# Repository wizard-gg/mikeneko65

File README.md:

# Mikeneko 65 V4

A simple 65% keyboard for DIYers. This project was derived from [kkatano's Bakeneko 65](https://github.com/kkatano/bakeneko-65).

## Updates

### Differences between Mikeneko 65 V3 and V4

- Switched pcb style from soldering to hotswap

### Differences between Bakeneko 65 V3 and Mikeneko 65 V3

- Added support for PCB screw ins stabilizer
- Switched MCU to ATmega32U4-MU(R) to cope with MCU supply shortage

## Features

- Single piece tray case
- O-ring gasket mount (Friction fit)
- [Unified Daughterboard](https://github.com/ai03-2725/Unified-Daughterboard) or [Simplified Daughterboard](https://github.com/kb-elmo/simplified-daughterboard)
- QMK firmware and VIA (For now, you can use Bakeneko 65's firmware as is)
- PCB designed with KiCAD 5.1.4

## Layouts

## Specs

- Dimensions: 315 x 110 x 30mm
- Front height: 18.5mm
- Home row height: 31mm(with GMK keycaps and bumpons)
- Typing angle: 6 degree
- Weight:
  - PLA Case: 390g
  - Aluminum Case: 760g
- O-ring gasket: VMQ-50(Silicone 50 duro) AS568-264

## Notes

- All files are to be used at your own risk
- As for stabilizers, both PCB snap ins and screw ins are supported

## Resources

- Documents: https://drive.google.com/drive/folders/1tddSihOS8Pgf1lTQOjHohYCl8efxXIeH
  - For now, you can refer Bakeneko 65's documents as is
  - Parts guide and other useful information
- Discord: https://discord.com/channels/927936241805189171/
  - Have fun with community members
  - Talk about Mikeneko builds and mods, and share your works
  - You can also contact me from there

## Special thanks to

- **kkatano** Open-sourced Bakeneko 65 and answered my questions in his community
- People who supported the development of Bakeneko series

## Also I should mention
- Many keyboard community members for giving me advice and feedback, thanks!

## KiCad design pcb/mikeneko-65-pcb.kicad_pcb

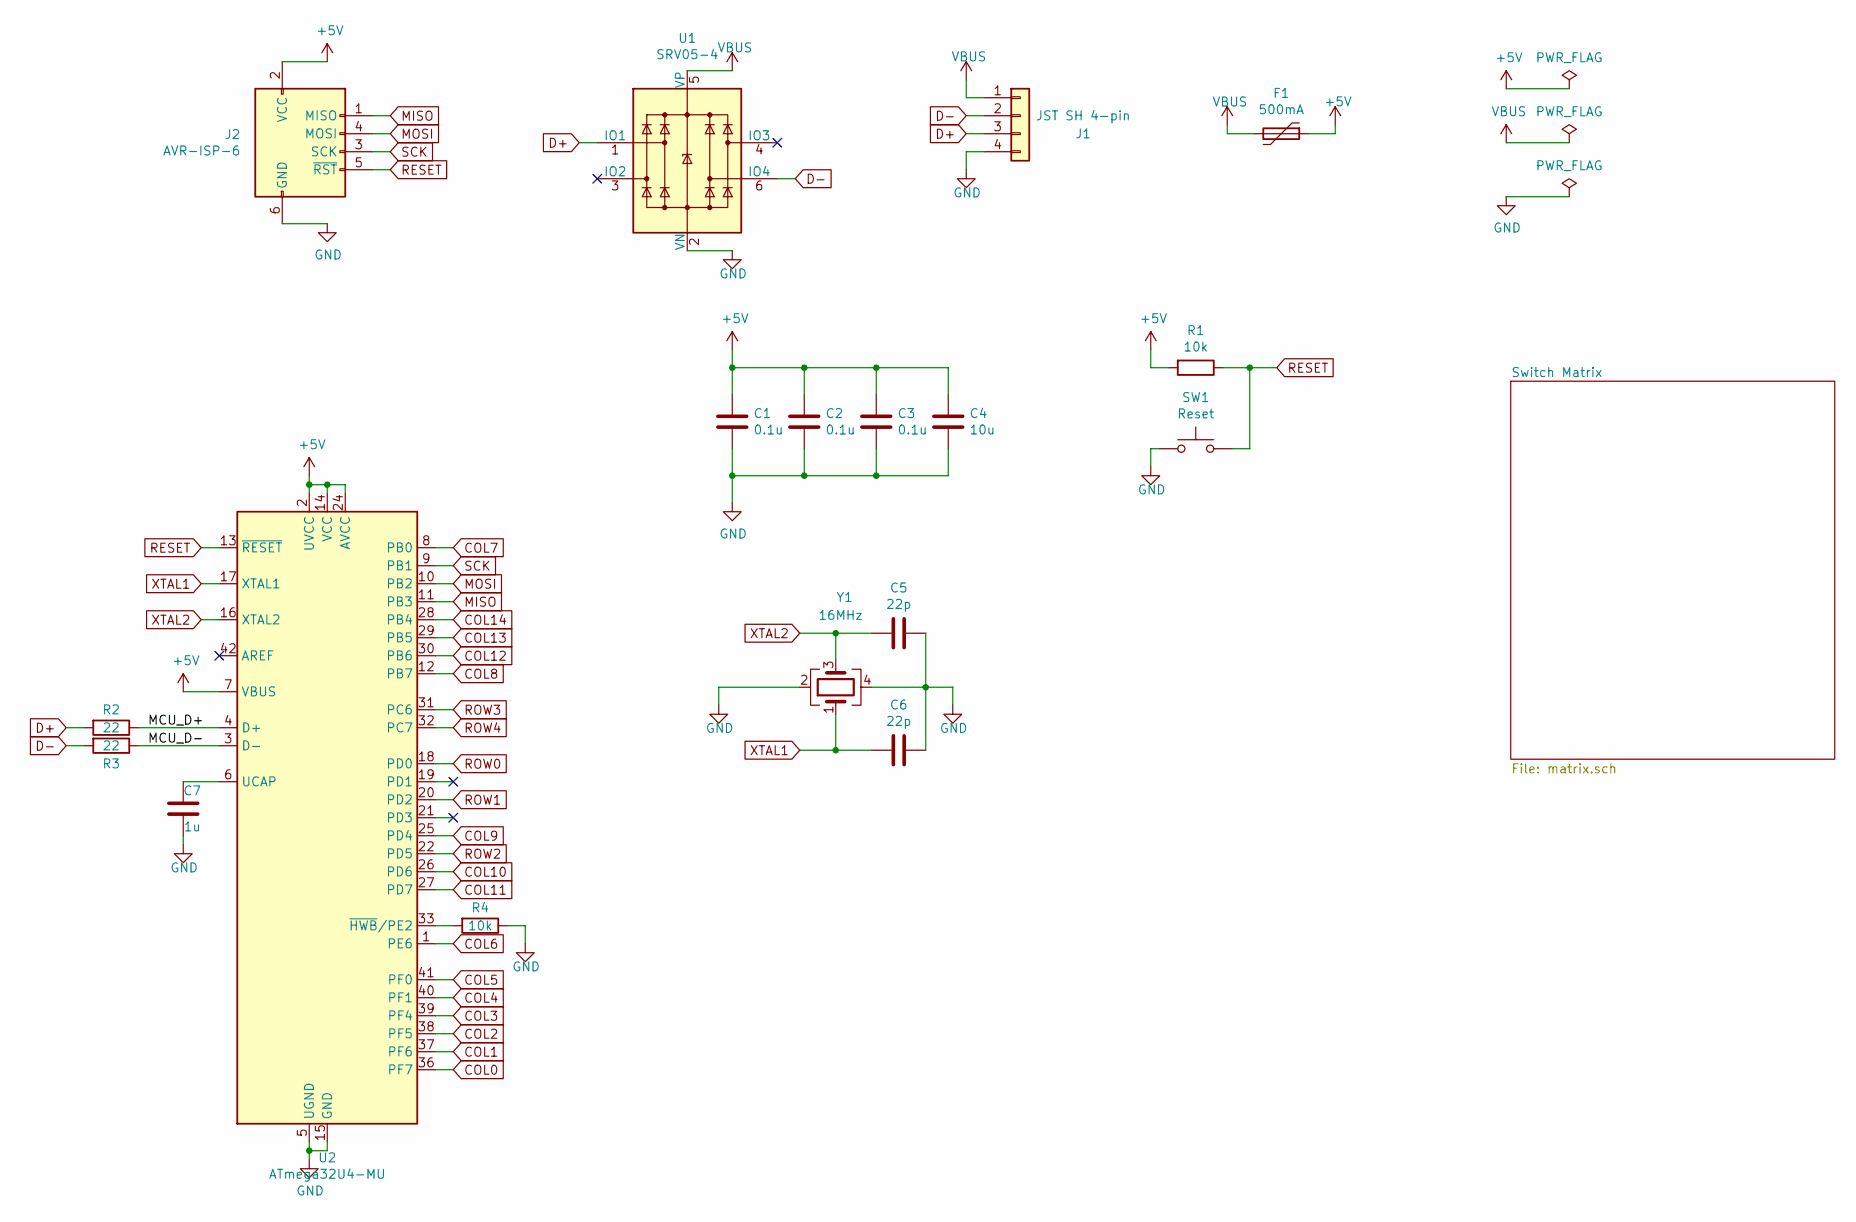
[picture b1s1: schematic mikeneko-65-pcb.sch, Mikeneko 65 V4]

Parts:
C1, C2, C3: 0.1u; C_0805_2012Metric; LCSC Part # C49678
C4: 10u; C_0805_2012Metric; LCSC Part # C15850
C5, C6: 22p; C_0805_2012Metric; LCSC Part # C1804
C7: 1u; C_0805_2012Metric; LCSC Part # C28323
F1: 500mA; Fuse_1206_3216Metric; LCSC Part # C70076
J1: JST SH 4-pin; JST_SH_SM04B-SRSS-TB_1x04-1MP_P1.00mm_Horizontal; LCSC Part # C160404
J2: AVR-ISP-6; ISP
R1, R4: 10k; R_0805_2012Metric; LCSC Part # C17414
R2, R3: 22; R_0805_2012Metric; LCSC Part # C17561
SW1: Reset; SW_SPST_TL3342; LCSC Part # C318884
U1: SRV05-4; SOT-23-6; LCSC Part # C85364
U2: ATmega32U4-MU; QFN-44-1EP_7x7mm_P0.5mm_EP5.2x5.2mm
Y1: 16MHz; Crystal_SMD_3225-4Pin_3.2x2.5mm; LCSC Part # C13738

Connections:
+5V: C1.1, C2.1, C3.1, C4.1, F1.1, J2.2 (VCC), R1.2, U2.2 (UVCC), U2.7 (VBUS), U2.14 (VCC), U2.24 (AVCC), U2.34 (VCC), U2.44 (AVCC)
/MCU_D+: R2.1, U2.4 (D+)
/MCU_D-: R3.1, U2.3 (D-)
COL0: U2.36 (PF7); also elsewhere on the board
COL1: U2.37 (PF6); also elsewhere on the board
COL2: U2.38 (PF5); also elsewhere on the board
COL3: U2.39 (PF4); also elsewhere on the board
COL4: U2.40 (PF1); also elsewhere on the board
COL5: U2.41 (PF0); also elsewhere on the board
COL6: U2.1 (PE6); also elsewhere on the board
COL7: U2.8 (PB0); also elsewhere on the board
COL8: U2.12 (PB7); also elsewhere on the board
COL9: U2.25 (PD4); also elsewhere on the board
COL10: U2.26 (PD6); also elsewhere on the board
COL11: U2.27 (PD7); also elsewhere on the board
COL12: U2.30 (PB6); also elsewhere on the board
COL13: U2.29 (PB5); also elsewhere on the board
COL14: U2.28 (PB4); also elsewhere on the board
D+: J1.3, R2.2, U1.1 (IO1)
D-: J1.2, R3.2, U1.6 (IO4)
GND: C1.2, C2.2, C3.2, C4.2, C5.1, C6.1, C7.2, J1.4, J2.6 (GND), R4.1, SW1.1, U1.2 (VN), U2.5 (UGND), U2.15 (GND), U2.23 (GND), U2.35 (GND), U2.43 (GND), U2.45 (GND), Y1.2, Y1.4
MISO: J2.1 (MISO), U2.11 (PB3)
MOSI: J2.4 (MOSI), U2.10 (PB2)
unnamed: C7.1, U2.6 (UCAP)
unnamed: R4.2, U2.33 (~HWB~/PE2)
RESET: J2.5 (~RST), R1.1, SW1.2, U2.13 (~RESET)
ROW0: U2.18 (PD0); also elsewhere on the board
ROW1: U2.20 (PD2); also elsewhere on the board
ROW2: U2.22 (PD5); also elsewhere on the board
ROW3: U2.31 (PC6); also elsewhere on the board
ROW4: U2.32 (PC7); also elsewhere on the board
SCK: J2.3 (SCK), U2.9 (PB1)
VBUS: F1.2, J1.1, U1.5 (VP)
XTAL1: C6.2, U2.17 (XTAL1), Y1.1
XTAL2: C5.2, U2.16 (XTAL2), Y1.3

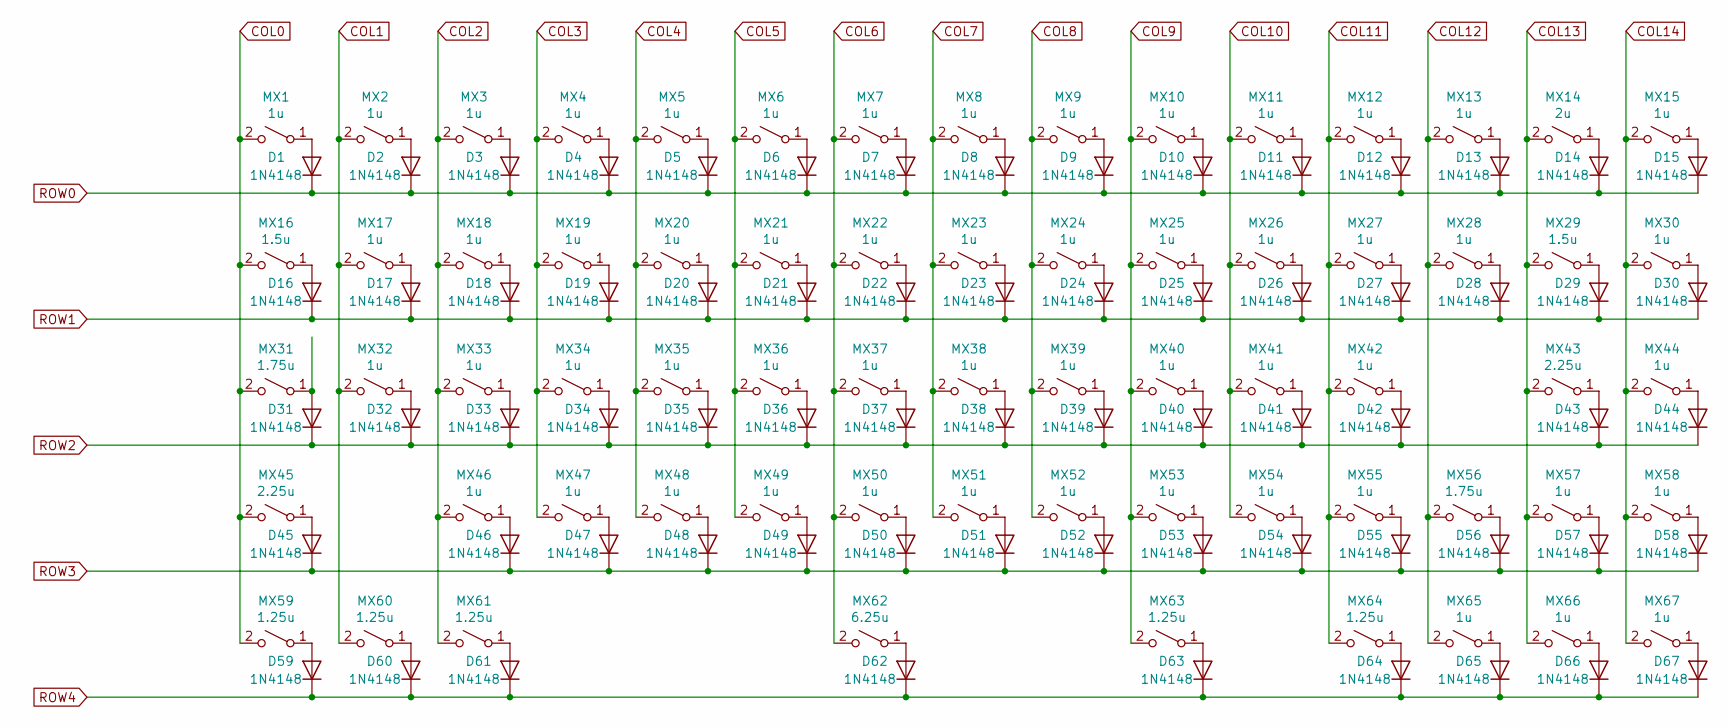
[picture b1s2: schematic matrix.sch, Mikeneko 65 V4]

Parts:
D1, D2, D3, D4, D5, D6, D7, D8, D9, D10, D11, D12, D13, D14, D15, D16, D17, D18, D19, D20, D21, D22, D23, D24, D25, D26, D27, D28, D29, D30, D31, D32, D33, D34, D35, D36, D37, D38, D39, D40, D41, D42, D43, D44, D45, D46, D47, D48, D49, D50, D51, D52, D53, D54, D55, D56, D57, D58, D59, D60, D61, D62, D63, D64, D65, D66, D67: 1N4148; D_SOD-123; LCSC Part # C81598
MX1, MX2, MX3, MX4, MX5, MX6, MX7, MX8, MX9, MX10, MX11, MX12, MX13, MX15, MX17, MX18, MX19, MX20, MX21, MX22, MX23, MX24, MX25, MX26, MX27, MX28, MX30, MX32, MX33, MX34, MX35, MX36, MX37, MX38, MX39, MX40, MX41, MX42, MX44, MX46, MX47, MX48, MX49, MX50, MX51, MX52, MX53, MX54, MX55, MX57, MX58, MX65, MX66, MX67: 1u; MXOnly-1U-Hotswap
MX14: 2u; MXOnly-2U-Hotswap
MX16, MX29: 1.5u; MXOnly-1.5U-Hotswap
MX31, MX56: 1.75u; MXOnly-1.75U-Hotswap
MX43, MX45: 2.25u; MXOnly-2.25U-Hotswap
MX59, MX60, MX61, MX63, MX64: 1.25u; MXOnly-1.25U-Hotswap
MX62: 6.25u; MXOnly-6.25U-Hotswap-ReversedStabilizers

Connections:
COL0: MX1.2 (B), MX16.2 (B), MX31.2 (B), MX45.2 (B), MX59.2 (B); also elsewhere on the board
COL1: MX2.2 (B), MX17.2 (B), MX32.2 (B), MX60.2 (B); also elsewhere on the board
COL2: MX3.2 (B), MX18.2 (B), MX33.2 (B), MX46.2 (B), MX61.2 (B); also elsewhere on the board
COL3: MX4.2 (B), MX19.2 (B), MX34.2 (B), MX47.2 (B); also elsewhere on the board
COL4: MX5.2 (B), MX20.2 (B), MX35.2 (B), MX48.2 (B); also elsewhere on the board
COL5: MX6.2 (B), MX21.2 (B), MX36.2 (B), MX49.2 (B); also elsewhere on the board
COL6: MX7.2 (B), MX22.2 (B), MX37.2 (B), MX50.2 (B), MX62.2 (B); also elsewhere on the board
COL7: MX8.2 (B), MX23.2 (B), MX38.2 (B), MX51.2 (B); also elsewhere on the board
COL8: MX9.2 (B), MX24.2 (B), MX39.2 (B), MX52.2 (B); also elsewhere on the board
COL9: MX10.2 (B), MX25.2 (B), MX40.2 (B), MX53.2 (B), MX63.2 (B); also elsewhere on the board
COL10: MX11.2 (B), MX26.2 (B), MX41.2 (B), MX54.2 (B); also elsewhere on the board
COL11: MX12.2 (B), MX27.2 (B), MX42.2 (B), MX55.2 (B), MX64.2 (B); also elsewhere on the board
COL12: MX13.2 (B), MX28.2 (B), MX56.2 (B), MX65.2 (B); also elsewhere on the board
COL13: MX14.2 (B), MX29.2 (B), MX43.2 (B), MX57.2 (B), MX66.2 (B); also elsewhere on the board
COL14: MX15.2 (B), MX30.2 (B), MX44.2 (B), MX58.2 (B), MX67.2 (B); also elsewhere on the board
unnamed: D1.2 (A), MX1.1 (A)
unnamed: D2.2 (A), MX2.1 (A)
unnamed: D3.2 (A), MX3.1 (A)
unnamed: D4.2 (A), MX4.1 (A)
unnamed: D5.2 (A), MX5.1 (A)
unnamed: D6.2 (A), MX6.1 (A)
unnamed: D7.2 (A), MX7.1 (A)
unnamed: D8.2 (A), MX8.1 (A)
unnamed: D9.2 (A), MX9.1 (A)
unnamed: D10.2 (A), MX10.1 (A)
unnamed: D11.2 (A), MX11.1 (A)
unnamed: D12.2 (A), MX12.1 (A)
unnamed: D13.2 (A), MX13.1 (A)
unnamed: D14.2 (A), MX14.1 (A)
unnamed: D15.2 (A), MX15.1 (A)
unnamed: D16.2 (A), MX16.1 (A)
unnamed: D17.2 (A), MX17.1 (A)
unnamed: D18.2 (A), MX18.1 (A)
unnamed: D19.2 (A), MX19.1 (A)
unnamed: D20.2 (A), MX20.1 (A)
unnamed: D21.2 (A), MX21.1 (A)
unnamed: D22.2 (A), MX22.1 (A)
unnamed: D23.2 (A), MX23.1 (A)
unnamed: D24.2 (A), MX24.1 (A)
unnamed: D25.2 (A), MX25.1 (A)
unnamed: D26.2 (A), MX26.1 (A)
unnamed: D27.2 (A), MX27.1 (A)
unnamed: D28.2 (A), MX28.1 (A)
unnamed: D29.2 (A), MX29.1 (A)
unnamed: D30.2 (A), MX30.1 (A)
unnamed: D31.2 (A), MX31.1 (A)
unnamed: D32.2 (A), MX32.1 (A)
unnamed: D33.2 (A), MX33.1 (A)
unnamed: D34.2 (A), MX34.1 (A)
unnamed: D35.2 (A), MX35.1 (A)
unnamed: D36.2 (A), MX36.1 (A)
unnamed: D37.2 (A), MX37.1 (A)
unnamed: D38.2 (A), MX38.1 (A)
unnamed: D39.2 (A), MX39.1 (A)
unnamed: D40.2 (A), MX40.1 (A)
unnamed: D41.2 (A), MX41.1 (A)
unnamed: D42.2 (A), MX42.1 (A)
unnamed: D43.2 (A), MX43.1 (A)
unnamed: D44.2 (A), MX44.1 (A)
unnamed: D45.2 (A), MX45.1 (A)
unnamed: D46.2 (A), MX46.1 (A)
unnamed: D47.2 (A), MX47.1 (A)
unnamed: D48.2 (A), MX48.1 (A)
unnamed: D49.2 (A), MX49.1 (A)
unnamed: D50.2 (A), MX50.1 (A)
unnamed: D51.2 (A), MX51.1 (A)
unnamed: D52.2 (A), MX52.1 (A)
unnamed: D53.2 (A), MX53.1 (A)
unnamed: D54.2 (A), MX54.1 (A)
unnamed: D55.2 (A), MX55.1 (A)
unnamed: D56.2 (A), MX56.1 (A)
unnamed: D57.2 (A), MX57.1 (A)
unnamed: D58.2 (A), MX58.1 (A)
unnamed: D59.2 (A), MX59.1 (A)
unnamed: D60.2 (A), MX60.1 (A)
unnamed: D61.2 (A), MX61.1 (A)
unnamed: D62.2 (A), MX62.1 (A)
unnamed: D63.2 (A), MX63.1 (A)
unnamed: D64.2 (A), MX64.1 (A)
unnamed: D65.2 (A), MX65.1 (A)
unnamed: D66.2 (A), MX66.1 (A)
unnamed: D67.2 (A), MX67.1 (A)
ROW0: D1.1 (K), D2.1 (K), D3.1 (K), D4.1 (K), D5.1 (K), D6.1 (K), D7.1 (K), D8.1 (K), D9.1 (K), D10.1 (K), D11.1 (K), D12.1 (K), D13.1 (K), D14.1 (K), D15.1 (K); also elsewhere on the board
ROW1: D16.1 (K), D17.1 (K), D18.1 (K), D19.1 (K), D20.1 (K), D21.1 (K), D22.1 (K), D23.1 (K), D24.1 (K), D25.1 (K), D26.1 (K), D27.1 (K), D28.1 (K), D29.1 (K), D30.1 (K); also elsewhere on the board
ROW2: D31.1 (K), D32.1 (K), D33.1 (K), D34.1 (K), D35.1 (K), D36.1 (K), D37.1 (K), D38.1 (K), D39.1 (K), D40.1 (K), D41.1 (K), D42.1 (K), D43.1 (K), D44.1 (K); also elsewhere on the board
ROW3: D45.1 (K), D46.1 (K), D47.1 (K), D48.1 (K), D49.1 (K), D50.1 (K), D51.1 (K), D52.1 (K), D53.1 (K), D54.1 (K), D55.1 (K), D56.1 (K), D57.1 (K), D58.1 (K); also elsewhere on the board
ROW4: D59.1 (K), D60.1 (K), D61.1 (K), D62.1 (K), D63.1 (K), D64.1 (K), D65.1 (K), D66.1 (K), D67.1 (K); also elsewhere on the board

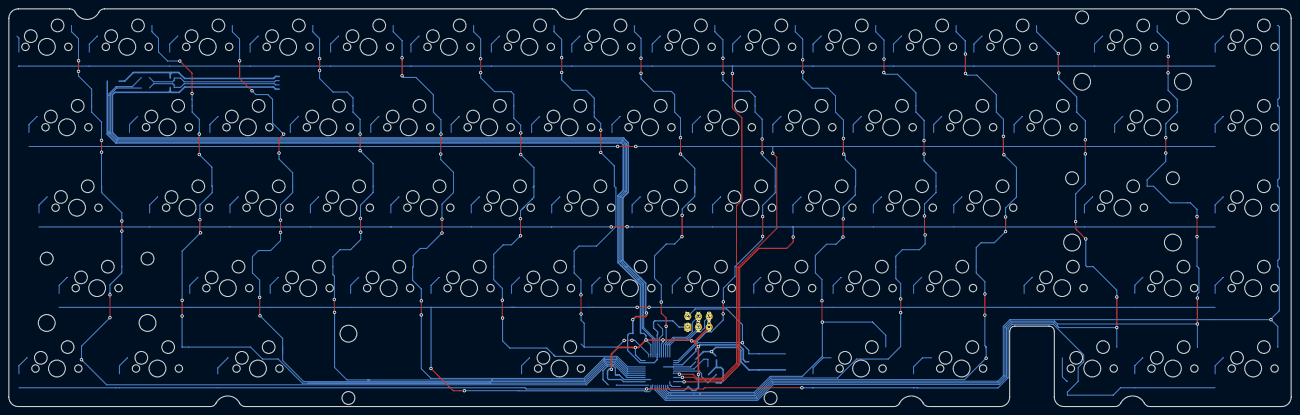
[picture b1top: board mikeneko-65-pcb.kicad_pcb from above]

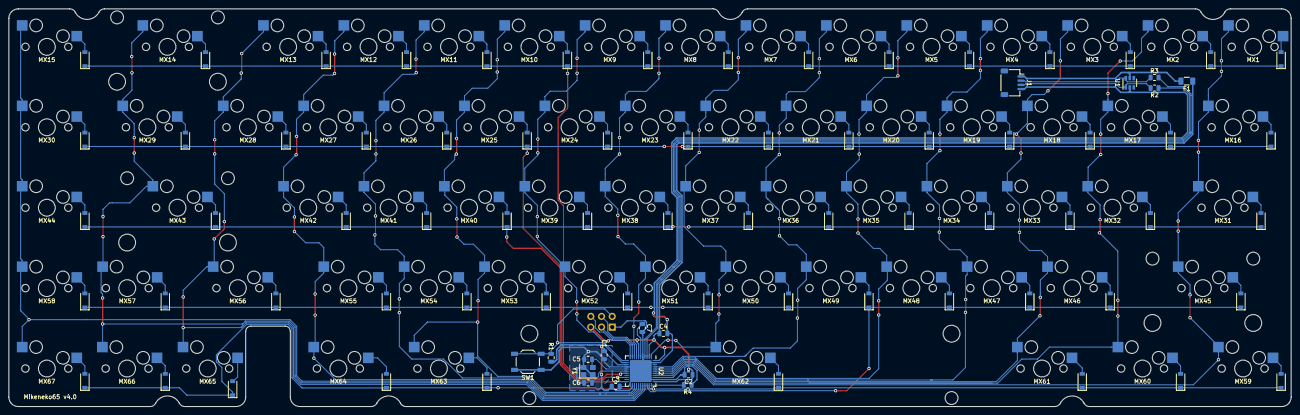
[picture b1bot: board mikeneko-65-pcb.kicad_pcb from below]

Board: 2 copper layers, 303.8 x 94.2 mm, 152 parts (84 on the bottom side), 102 nets.

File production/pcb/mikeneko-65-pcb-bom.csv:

Designator,Comment,Footprint,LCSC Part #
C1 C2 C3,0.1u,Capacitor_SMD:C_0805_2012Metric,C49678
C4,10u,Capacitor_SMD:C_0805_2012Metric,C15850
C5 C6,22p,Capacitor_SMD:C_0805_2012Metric,C1804
C7,1u,Capacitor_SMD:C_0805_2012Metric,C28323
D1 D2 D3 D4 D5 D6 D7 D8 D9 D10 D11 D12 D13 D14 D15 D16 D17 D18 D19 D20 D21 D22 D23 D24 D25 D26 D27 D28 D29 D30 D31 D32 D33 D34 D35 D36 D37 D38 D39 D40 D41 D42 D43 D44 D45 D46 D47 D48 D49 D50 D51 D52 D53 D54 D55 D56 D57 D58 D59 D60 D61 D62 D63 D64 D65 D66 D67,1N4148,Diode_SMD:D_SOD-123,C81598
F1,500mA,Fuse:Fuse_1206_3216Metric,C70076
J1,JST SH 4-pin,Connector_JST:JST_SH_SM04B-SRSS-TB_1x04-1MP_P1.00mm_Horizontal,C160404
R1 R4,10k,Resistor_SMD:R_0805_2012Metric,C17414
R2 R3,22,Resistor_SMD:R_0805_2012Metric,C17561
SW1,Reset,Button_Switch_SMD:SW_SPST_TL3342,C318884
U1,SRV05-4,Package_TO_SOT_SMD:SOT-23-6,C85364
U2,ATmega32U4-MU,Package_DFN_QFN:QFN-44-1EP_7x7mm_P0.5mm_EP5.2x5.2mm,C45874
Y1,16MHz,Crystal:Crystal_SMD_3225-4Pin_3.2x2.5mm,C13738

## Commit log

2022-01-02 bakeneko-65のdevelopブランチの20220102のコードをコミット。
2022-01-02 .gitignoreを追加。
2022-01-02 bakenekoをmikenekoに変換。
2022-01-02 回路図のmcuをatmega32u4-muに変更。
2022-01-02 回路図から基板を更新。
2022-01-02 atmega32u4-muの配線を修正。 配線の太さの定義を追加、配線間隔の最小値を0.127mmに変更
2022-01-04 pcbのgerberファイルとbomファイルとcplファイルを更新。
2022-01-04 見積もり用の図面(画像)ファイルを追加。 既存の図面(PDF)ファイルを削除。
2022-01-04 スクリューインタイプのスタビライザーに対応し、ガーバーファイルを更新。
2022-01-04 ドキュメントを更新。
2022-01-05 キーボードの画像を更新。
2022-01-05 不要なファイルを削除。
2022-01-06 ソケットに対応。
2022-01-08 配線を更新。
2022-01-08 V3をV4に変更。
2022-01-08 gerber、bom、cplファイルを更新。ファイル名からバージョンを除去。
2022-01-08 firmwareのコードを追加。
2022-01-08 README.mdの内容をV4に更新、キーレイアウト画像を更新。
2022-01-12 著作権表示を整理。

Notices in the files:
pcb/matrix.sch:
Copyright © 2020 kkatano
MIT License
